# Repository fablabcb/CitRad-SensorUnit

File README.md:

# CitRad - Citizen Science Traffic Radar 

Here you find all the sources about how to build our traffic counter radar system. Find more about the project in general on our [project page](https://community.fablab-cottbus.de/t/ueber-das-cityradar-projekt/453). Discussions about the prototype development you find [here](https://community.fablab-cottbus.de/t/cityradar-teensy-prototyp/492/9). Also we have a separate discussion page about the [development of the casing](https://community.fablab-cottbus.de/t/gehaeusebau-fuer-die-radarsensorelektronik/507).

More details are in the [Software README]() and the [Hardware README](https://github.com/fablabcb/CityRadar/tree/main/Hardware#readme).

## Archive

In the beginning we started to develop a low noise amplifier for the radar module that we didn't need in the end. You find all about this in the [low-noise-amplifier branch](https://github.com/fablabcb/CityRadar/tree/low-noise-amplifier) and on the [discussion page in our forum](https://community.fablab-cottbus.de/t/citrad-elektronik-entwicklung/454)

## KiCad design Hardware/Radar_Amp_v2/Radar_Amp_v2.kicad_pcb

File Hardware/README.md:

# CitRad 3D-Druck und Lasercut Teile

Die detaillierte Bauanleitung findet sich unter [citrad.de/docs/Bauanleitung](https://citrad.de/docs/bauanleitung/). 

Hier finden sich die Lasercut- und 3D-Druck Teile:

- Mit dem Lasercutter die Einlegeplatte 'CasingInlay.svg' aus 3mm Acryl oder ähnlichem schneiden. Bei mehreren `CasingInlay_6x.svg` verwenden.
- Die Mstbefestigung `MastFastening.svg` und die Abstandhalter `MastFasteningWasher.svg` aus 5mm Acryl oder ähnlichem schneiden.
- `SensorRadarMount.scad` in [OpenSCAD](https://openscad.org/) öffnen, als STL exportieren und dann 3D-drucken

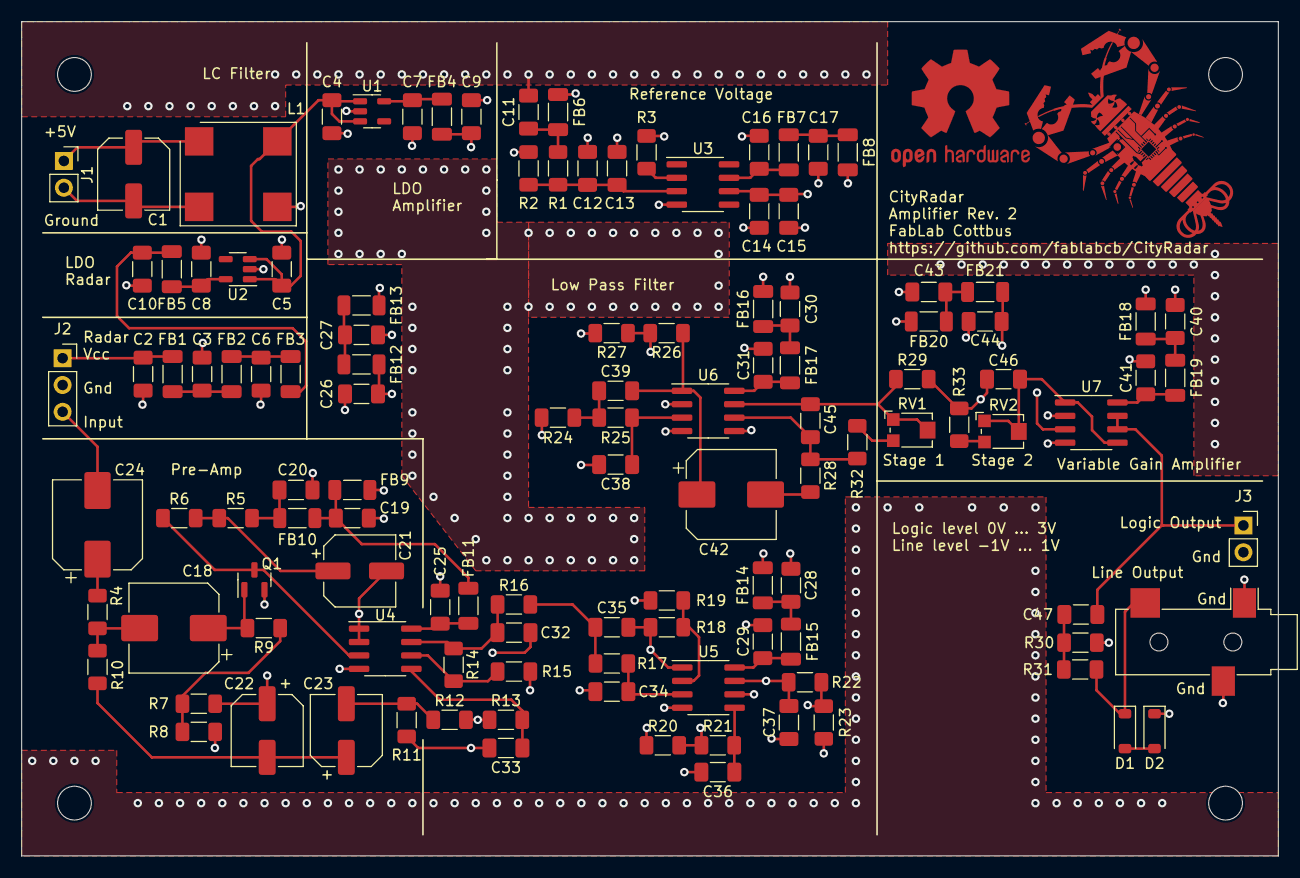
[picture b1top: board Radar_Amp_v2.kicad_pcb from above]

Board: 4 copper layers, 119.0 x 79.0 mm, 123 parts (0 on the bottom side), 67 nets.

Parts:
C1: 100µ; C_Elec_6.3x7.7
C2: 1n; C_1206_3216Metric_Pad1.33x1.80mm_HandSolder
C3, C13, C15, C16, C20, C25, C26, C29, C31, C41, C44: 100n; C_1206_3216Metric_Pad1.33x1.80mm_HandSolder
C4, C5, C6, C7, C8, C12, C14, C19: 10µ; C_1206_3216Metric_Pad1.33x1.80mm_HandSolder
C9, C10, C11, C17: 1µ; C_1206_3216Metric_Pad1.33x1.80mm_HandSolder
C18, C24, C42: 470µ; CP_Elec_8x10
C21, C22, C23: 220µ; C_Elec_6.3x7.7
C27, C28, C30, C40, C43: 1u; C_1206_3216Metric_Pad1.33x1.80mm_HandSolder
C32, C33, C34, C35, C36, C37, C38, C39: 16n; C_1206_3216Metric_Pad1.33x1.80mm_HandSolder
C45, C46: 4p7; C_1206_3216Metric_Pad1.33x1.80mm_HandSolder
C47: 47µ; C_1206_3216Metric_Pad1.33x1.80mm_HandSolder
D1, D2: 1V8; D_SOD-123
FB1, FB2, FB3, FB4, FB5, FB6, FB7, FB8, FB9, FB10, FB11, FB12, FB13, FB14, FB15, FB16, FB17, FB18, FB19, FB20, FB21: 1k@100MHz; L_1206_3216Metric_Pad1.22x1.90mm_HandSolder
H1, H2, H3, H4: MountingHole; MountingHole_3.2mm_M3
J1: Conn_Supply; PinSocket_1x02_P2.54mm_Vertical
J2: Conn_Radar; PinSocket_1x03_P2.54mm_Vertical
J3: Conn_Output_I; PinSocket_1x02_P2.54mm_Vertical
J4: Jack_Output; Jack_3.5mm_CUI_SJ-3523-SMT_Horizontal
L1: Choke_1m; Bourns_SRF1006
Q1: BC847; SOT-23
R1, R2, R9, R10, R11: 1k; R_1206_3216Metric_Pad1.30x1.75mm_HandSolder
R3: 4k99; R_1206_3216Metric_Pad1.30x1.75mm_HandSolder
R4: 10; R_1206_3216Metric_Pad1.30x1.75mm_HandSolder
R5, R6: 2k2; R_1206_3216Metric_Pad1.30x1.75mm_HandSolder
R7: 820; R_1206_3216Metric_Pad1.30x1.75mm_HandSolder
R8: 470; R_1206_3216Metric_Pad1.30x1.75mm_HandSolder
R12, R23: 549; R_1206_3216Metric_Pad1.30x1.75mm_HandSolder
R13: 1k78; R_1206_3216Metric_Pad1.30x1.75mm_HandSolder
R14, R24: 2k15; R_1206_3216Metric_Pad1.30x1.75mm_HandSolder
R15: 976; R_1206_3216Metric_Pad1.30x1.75mm_HandSolder
R16: 365; R_1206_3216Metric_Pad1.30x1.75mm_HandSolder
R17: 2k67; R_1206_3216Metric_Pad1.30x1.75mm_HandSolder
R18: 2k49; R_1206_3216Metric_Pad1.30x1.75mm_HandSolder
R19: 649; R_1206_3216Metric_Pad1.30x1.75mm_HandSolder
R20: 316; R_1206_3216Metric_Pad1.30x1.75mm_HandSolder
R21: 3k09; R_1206_3216Metric_Pad1.30x1.75mm_HandSolder
R22: 2k55; R_1206_3216Metric_Pad1.30x1.75mm_HandSolder
R25: 4k53; R_1206_3216Metric_Pad1.30x1.75mm_HandSolder
R26: 357; R_1206_3216Metric_Pad1.30x1.75mm_HandSolder
R27: 2k74; R_1206_3216Metric_Pad1.30x1.75mm_HandSolder
R28, R29, R32, R33: 100; R_1206_3216Metric_Pad1.30x1.75mm_HandSolder
R30: 10k; R_1206_3216Metric_Pad1.30x1.75mm_HandSolder
R31: 300; R_1206_3216Metric_Pad1.30x1.75mm_HandSolder
RV1, RV2: 10k; Potentiometer_Bourns_TC33X_Vertical
SYM1: Logo_Open_Hardware_Small; OSHW-Logo2_14.6x12mm_Copper
U1, U2: TPS7A2033PDBVR; SOT-23-5
U3: AD8031; SOIC-8_3.9x4.9mm_P1.27mm
U4, U5, U6, U7: AD8656; SOIC-8_3.9x4.9mm_P1.27mm

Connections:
+3.3V: C10.1, FB3.2, FB5.2
+3.3VA: C9.1, FB4.2, FB6.2, FB8.1, FB9.2, FB14.2, FB16.2, FB18.2
/Low-Pass Filter (40dB)/Vref_LPF: C26.1, C33.2, C34.2, C36.2, C38.2, FB12.1, R11.1, R15.2, R19.2, R23.2, R27.2
/Low-Pass Filter (40dB)/input_lpf: C23.2, R11.2, R12.1
/Low-Pass Filter (40dB)/output_lpf: C39.2, C42.1, R26.1, U6.1
/Output Connectors/input_output: C47.1, J3.1, U7.6 (-), U7.7
/Radar_I: C24.2, J2.3
/Vref: C14.1, C15.1, FB13.2, FB20.2, R3.2, U3.6 (Out)
GND: C2.2, C3.2, C4.2, C5.2, C6.2, C7.2, C8.2, C9.2, C10.2, C11.2, C12.2, C13.2, C14.2, C15.2, C16.2, C17.2, C19.2, C20.2, C25.2, C26.2, C27.2, C28.2, C29.2, C30.2, C31.2, C40.2, C41.2, C43.2, C44.2, D2.1 (K), J2.2, J3.2, J4.R, J4.S, L1.3, Q1.2 (E), R2.2, R8.1, R30.1, U1.2 (GND), U2.2 (GND), U3.4 (Vs-), U4.4 (V-), U5.4 (V-), U6.4 (V-), U7.4 (V-)
unnamed: C3.1, FB1.2, FB2.1
unnamed: C6.1, FB2.2, FB3.1
unnamed: C11.1, FB6.1, R1.1
unnamed: C17.1, FB7.2, FB8.2
unnamed: C18.2, R4.2, R10.2
unnamed: C19.1, FB9.1, FB10.2, FB11.2
unnamed: C20.1, FB10.1, R5.2
unnamed: C21.1, R5.1, R6.2
unnamed: C22.2, C23.1, R10.1
unnamed: C24.1, R4.1
unnamed: C27.1, FB12.2, FB13.1
unnamed: C28.1, FB14.1, FB15.2
unnamed: C30.1, FB16.1, FB17.2
unnamed: C32.1, R12.2, R13.1
unnamed: C32.2, R14.1, R16.1, U4.7
unnamed: C35.1, R16.2, R17.1
unnamed: C35.2, R18.1, R20.1, U5.1
unnamed: C37.1, R20.2, R21.1
unnamed: C37.2, R22.1, R24.1, U5.7
unnamed: C39.1, R24.2, R25.1
unnamed: C40.1, FB18.1, FB19.2
unnamed: C42.2, R28.1
unnamed: C43.1, FB20.1, FB21.2
unnamed: C45.2, R29.1, RV1.1, RV1.2, U6.7
unnamed: C47.2, R30.2, R31.1
unnamed: D1.2 (A), D2.2 (A)
unnamed: D1.1 (K), J4.T, R31.2
unnamed: C1.1, J1.1, L1.1
unnamed: C1.2, J1.2, L1.4
unnamed: C2.1, FB1.1, J2.1
unnamed: C18.1, Q1.1 (B), R9.2
unnamed: Q1.3 (C), R6.1, U4.3 (+)
unnamed: R7.1, R8.2, R9.1
unnamed: R32.2, RV1.3
unnamed: R33.2, RV2.3
unnamed: C4.1, C5.1, L1.2, U1.1 (IN), U1.3 (EN), U2.1 (IN), U2.3 (EN)
unnamed: C7.1, FB4.1, U1.5 (OUT)
unnamed: C8.1, FB5.1, U2.5 (OUT)
unnamed: C12.1, C13.1, R1.2, R2.1, U3.3 (IN+)
unnamed: R3.1, U3.2 (IN-)
unnamed: C16.1, FB7.1, U3.7 (Vs+)
unnamed: C21.2, C22.1, R7.2, U4.1, U4.2 (-)
unnamed: C33.1, R13.2, U4.5 (+)
unnamed: R14.2, R15.1, U4.6 (-)
unnamed: C25.1, FB11.1, U4.8 (V+)
unnamed: C34.1, R17.2, U5.3 (+)
unnamed: R18.2, R19.1, U5.2 (-)
unnamed: C36.1, R21.2, U5.5 (+)
unnamed: R22.2, R23.1, U5.6 (-)
unnamed: C29.1, FB15.1, U5.8 (V+)
unnamed: C38.1, R25.2, U6.3 (+)
unnamed: R26.2, R27.1, U6.2 (-)
unnamed: C44.1, FB21.1, U6.5 (+), U7.3 (+)
unnamed: C45.1, R28.2, R32.1, U6.6 (-)
unnamed: C31.1, FB17.1, U6.8 (V+)
unnamed: C46.1, R29.2, R33.1, U7.2 (-)
unnamed: C46.2, RV2.1, RV2.2, U7.1, U7.5 (+)
unnamed: C41.1, FB19.1, U7.8 (V+)

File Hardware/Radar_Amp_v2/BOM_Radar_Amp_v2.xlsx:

Qty | Reference(s) | Value | Footprint | Manufacture #
1 | C1 | 100µ | Capacitor_SMD:C_Elec_6.3x7.7 | 865060343005
1 | C2 | 1n | Capacitor_SMD:C_1206_3216Metric_Pad1.33x1.80mm_HandSolder | C1206C102M5RACTU
11 | C3, C13, C15, C16, C20, C25, C26, C29, C31, C41, C44 | 100n | Capacitor_SMD:C_1206_3216Metric_Pad1.33x1.80mm_HandSolder | C1206C104M5RACTU
8 | C4, C5, C6, C7, C8, C12, C14, C19 | 10µ | Capacitor_SMD:C_1206_3216Metric_Pad1.33x1.80mm_HandSolder | C1206C106K4RACTU
4 | C9, C10, C11, C17 | 1µ | Capacitor_SMD:C_1206_3216Metric_Pad1.33x1.80mm_HandSolder | C1206C105K4RACTU
3 | C18, C24, C42 | 470µ | Capacitor_SMD:CP_Elec_8x10 | 865080353015
3 | C21, C22, C23 | 220µ | Capacitor_SMD:C_Elec_6.3x7.7 | 865060345007
5 | C27, C28, C30, C40, C43 | 1u | Capacitor_SMD:C_1206_3216Metric_Pad1.33x1.80mm_HandSolder | C1206C104M5RACTU
8 | C32, C33, C34, C35, C36, C37, C38, C39 | 16n | Capacitor_SMD:C_1206_3216Metric_Pad1.33x1.80mm_HandSolder | GRM3195C1H163JA01D
2 | C45, C46 | 4p7 | Capacitor_SMD:C_1206_3216Metric_Pad1.33x1.80mm_HandSolder | C1206C479C2GACTU
1 | C47 | 47µ | Capacitor_SMD:C_1206_3216Metric_Pad1.33x1.80mm_HandSolder | C3216X5R1E476M160AC
2 | D1, D2 | 1V8 | Diode_SMD:D_SOD-123 | MMSZ4678-TP
21 | FB1, FB2, FB3, FB4, FB5, FB6, FB7, FB8, FB9, FB10, FB11, FB12, FB13, FB14, FB15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 | 1k@100MHz | Inductor_SMD:L_1206_3216Metric_Pad1.22x1.90mm_HandSolder | BLM31KN102SN1L
1 | J4 | Jack_Output | Connector_Audio:Jack_3.5mm_CUI_SJ-3523-SMT_Horizontal | SJ-3523-SMT-TR
1 | L1 | Choke_1m | radaramp_footprints:Bourns_SRF1006 | SRF1006-102Y
1 | Q1 | BC847 | Package_TO_SOT_SMD:SOT-23 | BC847C,215
5 | R1, R2, R9, R10, R11 | 1k | Resistor_SMD:R_1206_3216Metric_Pad1.30x1.75mm_HandSolder | CR1206-FX-1002ELF
1 | R3 | 4k99 | Resistor_SMD:R_1206_3216Metric_Pad1.30x1.75mm_HandSolder | CR1206-FX-4991ELF
1 | R4 | 10 | Resistor_SMD:R_1206_3216Metric_Pad1.30x1.75mm_HandSolder | CR1206-FX-10R0ELF
2 | R5, R6 | 2k2 | Resistor_SMD:R_1206_3216Metric_Pad1.30x1.75mm_HandSolder | CR1206-FX-2202ELF
1 | R7 | 820 | Resistor_SMD:R_1206_3216Metric_Pad1.30x1.75mm_HandSolder | CR1206-FX-8200ELF
1 | R8 | 470 | Resistor_SMD:R_1206_3216Metric_Pad1.30x1.75mm_HandSolder | CR1206-FX-4700ELF
2 | R12, R23 | 549 | Resistor_SMD:R_1206_3216Metric_Pad1.30x1.75mm_HandSolder | CR1206-FX-5490ELF
1 | R13 | 1k78 | Resistor_SMD:R_1206_3216Metric_Pad1.30x1.75mm_HandSolder | CR1206-FX-1781ELF
2 | R14, R24 | 2k15 | Resistor_SMD:R_1206_3216Metric_Pad1.30x1.75mm_HandSolder | CR1206-FX-2151ELF
1 | R15 | 976 | Resistor_SMD:R_1206_3216Metric_Pad1.30x1.75mm_HandSolder | RC1206FR-07976RL
1 | R16 | 365 | Resistor_SMD:R_1206_3216Metric_Pad1.30x1.75mm_HandSolder | CR1206-FX-3650ELF
1 | R17 | 2k67 | Resistor_SMD:R_1206_3216Metric_Pad1.30x1.75mm_HandSolder | CR1206-FX-2671ELF
1 | R18 | 2k49 | Resistor_SMD:R_1206_3216Metric_Pad1.30x1.75mm_HandSolder | CR1206-FX-2491ELF
1 | R19 | 649 | Resistor_SMD:R_1206_3216Metric_Pad1.30x1.75mm_HandSolder | CR1206-FX-6490ELF
1 | R20 | 316 | Resistor_SMD:R_1206_3216Metric_Pad1.30x1.75mm_HandSolder | CR1206-FX-3160ELF
1 | R21 | 3k09 | Resistor_SMD:R_1206_3216Metric_Pad1.30x1.75mm_HandSolder | CR1206-FX-3091ELF
1 | R22 | 2k55 | Resistor_SMD:R_1206_3216Metric_Pad1.30x1.75mm_HandSolder | CR1206-FX-2551ELF
1 | R25 | 4k53 | Resistor_SMD:R_1206_3216Metric_Pad1.30x1.75mm_HandSolder | CR1206-FX-4531ELF
1 | R26 | 357 | Resistor_SMD:R_1206_3216Metric_Pad1.30x1.75mm_HandSolder | CR1206-FX-3570ELF
1 | R27 | 2k74 | Resistor_SMD:R_1206_3216Metric_Pad1.30x1.75mm_HandSolder | CR1206-FX-2741ELF
4 | R28, R29, R32, R33 | 100 | Resistor_SMD:R_1206_3216Metric_Pad1.30x1.75mm_HandSolder | CR1206-FX-1000ELF
1 | R30 | 10k | Resistor_SMD:R_1206_3216Metric_Pad1.30x1.75mm_HandSolder | CR1206-FX-1002ELF
1 | R31 | 300 | Resistor_SMD:R_1206_3216Metric_Pad1.30x1.75mm_HandSolder | CR1206-FX-3000ELF
2 | RV1, RV2 | 10k | Potentiometer_SMD:Potentiometer_Bourns_TC33X_Vertical | TC33X-2-103E
2 | U1, U2 | TPS7A2033PDBVR | Package_TO_SOT_SMD:SOT-23-5 | TPS7A2033PDBVR
1 | U3 | AD8031 | Package_SO:SOIC-8_3.9x4.9mm_P1.27mm | AD8031ARZ
4 | U4, U5, U6, U7 | AD8656 | Package_SO:SOIC-8_3.9x4.9mm_P1.27mm | AD8656ARZ

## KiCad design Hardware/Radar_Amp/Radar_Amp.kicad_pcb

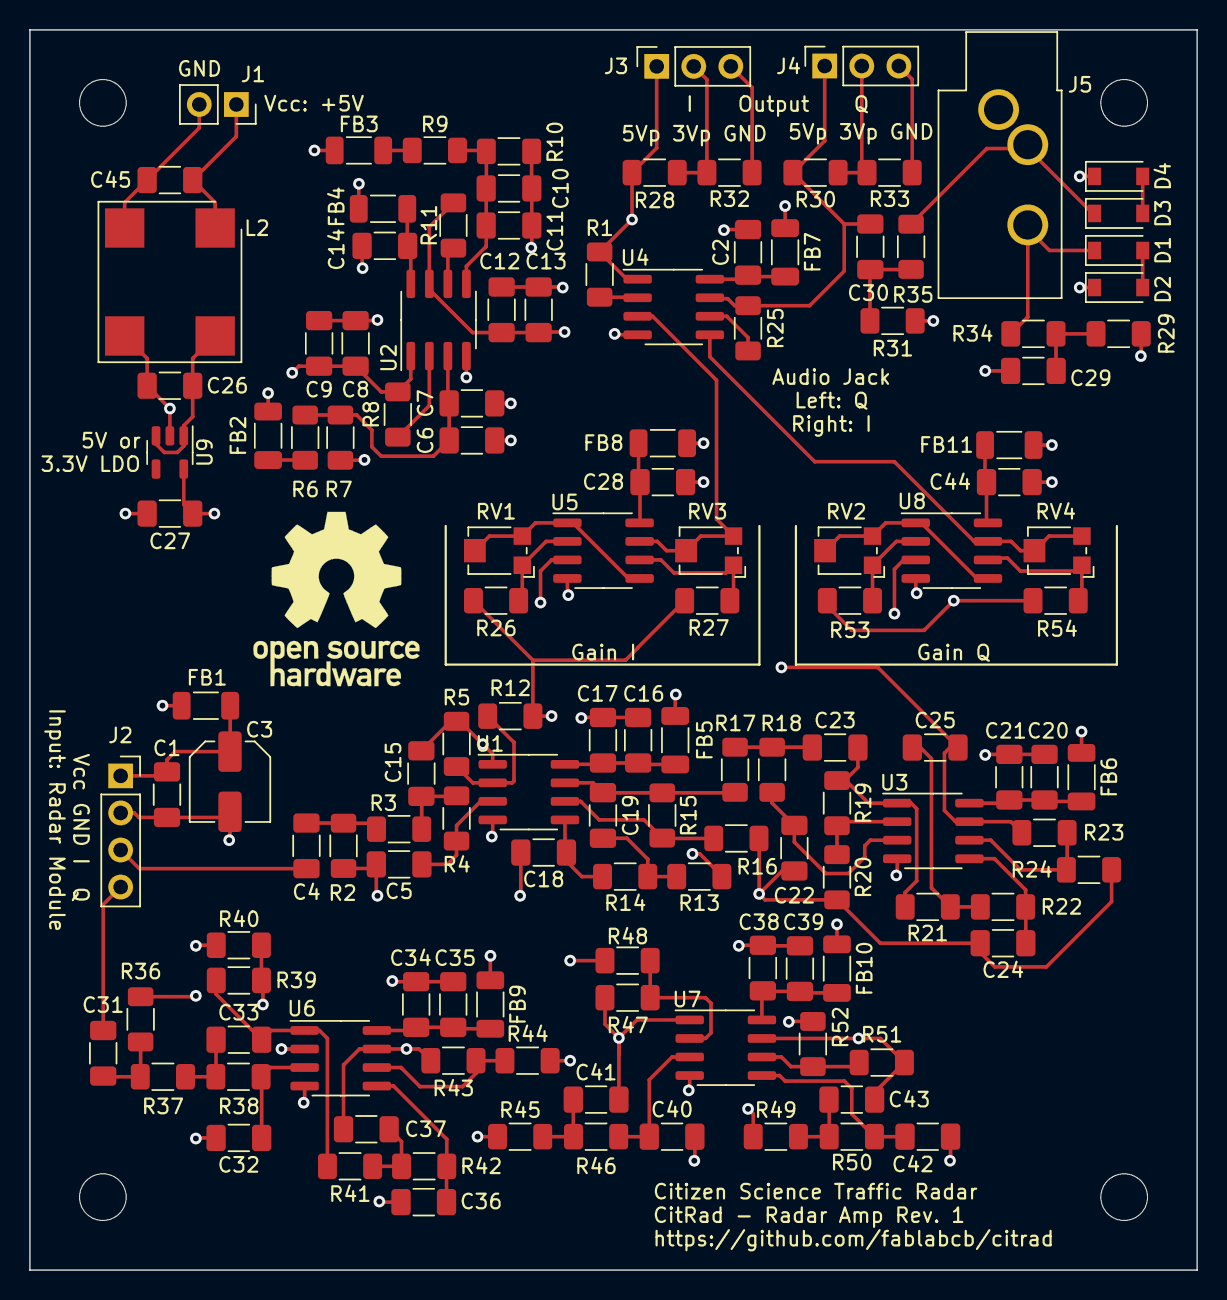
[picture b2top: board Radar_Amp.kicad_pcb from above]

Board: 4 copper layers, 80.0 x 85.0 mm, 137 parts (0 on the bottom side), 78 nets.

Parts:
C1, C7, C9, C11, C13, C17, C21, C35, C39: 100n; C_1206_3216Metric_Pad1.33x1.80mm_HandSolder
C2, C14, C26, C27, C28, C44, C45: 1µ; C_1206_3216Metric_Pad1.33x1.80mm_HandSolder
C3: 10µ; C_Elec_5x5.4
C4, C29, C30, C31: 22µ; C_1206_3216Metric_Pad1.33x1.80mm_HandSolder
C5, C15, C18, C19, C22, C23, C25, C32, C33, C36, C37, C40, C41, C43: 16n; C_1206_3216Metric_Pad1.33x1.80mm_HandSolder
C6, C8, C10, C12, C16, C20, C34, C38: 10µ; C_1206_3216Metric_Pad1.33x1.80mm_HandSolder
C24, C42: 1n6; C_1206_3216Metric_Pad1.33x1.80mm_HandSolder
D1, D2, D3, D4: 1V8; D_SOD-123
FB1, FB2, FB3, FB4, FB5, FB6, FB7, FB8, FB9, FB10, FB11: 1k@100MHz; L_1206_3216Metric_Pad1.22x1.90mm_HandSolder
H1, H2, H3, H4: MountingHole; MountingHole_3.2mm_M3
J1: Conn_Supply; PinSocket_1x02_P2.54mm_Vertical
J2: Conn_Radar; PinSocket_1x04_P2.54mm_Vertical
J3: Conn_Output_I; PinSocket_1x03_P2.54mm_Vertical
J4: Conn_Output_Q; PinSocket_1x03_P2.54mm_Vertical
J5: AudioJack3; Jack_3.5mm_CUI_SJ1-3533NG_Horizontal_CircularHoles
L2: Choke_1m; Bourns_SRF1006
R1, R8, R11, R25: 4k99; R_1206_3216Metric_Pad1.30x1.75mm_HandSolder
R2, R6, R7, R9, R10, R29, R31, R36: 10k; R_1206_3216Metric_Pad1.30x1.75mm_HandSolder
R3, R20, R37, R48: 549; R_1206_3216Metric_Pad1.30x1.75mm_HandSolder
R4, R28, R30, R38: 1k78; R_1206_3216Metric_Pad1.30x1.75mm_HandSolder
R5, R21, R39, R49: 2k15; R_1206_3216Metric_Pad1.30x1.75mm_HandSolder
R12, R40: 976; R_1206_3216Metric_Pad1.30x1.75mm_HandSolder
R13, R41: 365; R_1206_3216Metric_Pad1.30x1.75mm_HandSolder
R14, R32, R33, R42: 2k67; R_1206_3216Metric_Pad1.30x1.75mm_HandSolder
R15, R43: 2k49; R_1206_3216Metric_Pad1.30x1.75mm_HandSolder
R16, R44: 649; R_1206_3216Metric_Pad1.30x1.75mm_HandSolder
R17, R45: 316; R_1206_3216Metric_Pad1.30x1.75mm_HandSolder
R18, R46: 3k09; R_1206_3216Metric_Pad1.30x1.75mm_HandSolder
R19, R47: 2k55; R_1206_3216Metric_Pad1.30x1.75mm_HandSolder
R22, R50: 4k53; R_1206_3216Metric_Pad1.30x1.75mm_HandSolder
R23, R51: 357; R_1206_3216Metric_Pad1.30x1.75mm_HandSolder
R24, R52: 2k74; R_1206_3216Metric_Pad1.30x1.75mm_HandSolder
R26, R27, R34, R35, R53, R54: 300; R_1206_3216Metric_Pad1.30x1.75mm_HandSolder
RV1, RV2, RV3, RV4: R_Potentiometer; Potentiometer_Bourns_TC33X_Vertical
U1, U6: OPA_LNA_1; SOIC-8_3.9x4.9mm_P1.27mm
U2: OPA_REF; SOIC-8_3.9x4.9mm_P1.27mm
U3, U7: OPA_LNA_2; SOIC-8_3.9x4.9mm_P1.27mm
U4: OPA_DRIVER; SOIC-8_3.9x4.9mm_P1.27mm
U5, U8: OPA_VGA; SOIC-8_3.9x4.9mm_P1.27mm
U9: TPS7A20; SOT-23-5

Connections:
+5V: C27.1, FB1.2, FB2.2, FB3.2, FB4.1, FB5.1, FB6.1, FB7.1, FB8.1, FB9.1, FB10.1, FB11.1, U9.5 (OUT)
/LNA+LPF1/Output: C43.2, R51.1, U7.7, U8.3 (+)
/LNA+LPF/Output: C25.2, R23.1, U3.7, U5.3 (+)
/Output/I: C29.1, J3.1, R1.2, R28.1, U4.1
/Output/Q: C30.1, J4.1, R25.2, R30.1, U4.7
/Radar_I: C4.1, J2.3
/Radar_Q: C31.1, J2.4
/VGA1/Output: RV4.2, RV4.3, U4.5 (+), U8.7
/VGA/Output: RV3.2, RV3.3, U4.3 (+), U5.7
/Vref1: C5.2, C8.1, C9.1, C18.2, C22.2, C24.2, R2.2, R8.2, R12.2, R16.2, R20.2, R24.2, R26.1, R27.1, U2.1
/Vref2: C12.1, C13.1, C32.2, C36.2, C40.2, C42.2, R11.2, R36.2, R40.2, R44.2, R48.2, R52.2, R53.1, R54.1, U2.7
GND: C1.2, C2.2, C3.2, C6.2, C7.2, C8.2, C9.2, C10.2, C11.2, C12.2, C13.2, C14.2, C16.2, C17.2, C20.2, C21.2, C26.2, C27.2, C28.2, C34.2, C35.2, C38.2, C39.2, C44.2, D2.1 (K), D4.1 (K), J2.2, J3.3, J4.3, J5.S, L2.3, R7.2, R10.2, R29.1, R31.1, R32.1, R33.1, U1.4 (V-), U2.4 (V-), U3.4 (V-), U4.4 (V-), U5.4 (V-), U6.4 (V-), U7.4 (V-), U8.4 (V-), U9.2 (GND)
unnamed: C1.1, C3.1, FB1.1, J2.1
unnamed: C2.1, FB7.2, U4.8 (V+)
unnamed: C4.2, R2.1, R3.1
unnamed: C5.1, R4.2, U1.3 (+)
unnamed: C6.1, C7.1, R6.2, R7.1, U2.3 (+)
unnamed: C10.1, C11.1, R9.2, R10.1, U2.5 (+)
unnamed: C14.1, FB4.2, U2.8 (V+)
unnamed: C15.1, R3.2, R4.1
unnamed: C15.2, R5.1, R13.1, U1.1
unnamed: C16.1, C17.1, FB5.2, U1.8 (V+)
unnamed: C18.1, R14.2, U1.5 (+)
unnamed: C19.1, R13.2, R14.1
unnamed: C19.2, R15.1, R17.1, U1.7
unnamed: C20.1, C21.1, FB6.2, U3.8 (V+)
unnamed: C22.1, R18.2, U3.3 (+)
unnamed: C23.1, R17.2, R18.1
unnamed: C23.2, R19.1, R21.1, U3.1
unnamed: C24.1, R22.2, U3.5 (+)
unnamed: C25.1, R21.2, R22.1
unnamed: C28.1, FB8.2, U5.8 (V+)
unnamed: C29.2, R29.2, R34.1
unnamed: C30.2, R31.2, R35.1
unnamed: C31.2, R36.1, R37.1
unnamed: C32.1, R38.2, U6.3 (+)
unnamed: C33.1, R37.2, R38.1
unnamed: C33.2, R39.1, R41.1, U6.1
unnamed: C34.1, C35.1, FB9.2, U6.8 (V+)
unnamed: C36.1, R42.2, U6.5 (+)
unnamed: C37.1, R41.2, R42.1
unnamed: C37.2, R43.1, R45.1, U6.7
unnamed: C38.1, C39.1, FB10.2, U7.8 (V+)
unnamed: C40.1, R46.2, U7.3 (+)
unnamed: C41.1, R45.2, R46.1
unnamed: C41.2, R47.1, R49.1, U7.1
unnamed: C42.1, R50.2, U7.5 (+)
unnamed: C43.1, R49.2, R50.1
unnamed: C44.1, FB11.2, U8.8 (V+)
unnamed: C45.1, J1.1, L2.1
unnamed: C45.2, J1.2, L2.4
unnamed: D1.1 (K), J5.R, R34.2
unnamed: D1.2 (A), D2.2 (A)
unnamed: D3.1 (K), J5.T, R35.2
unnamed: D3.2 (A), D4.2 (A)
unnamed: FB2.1, R6.1
unnamed: FB3.1, R9.1
unnamed: J3.2, R28.2, R32.2
unnamed: J4.2, R30.2, R33.2
unnamed: C26.1, L2.2, U9.1 (IN), U9.3 (EN)
unnamed: R1.1, U4.2 (-)
unnamed: R8.1, U2.2 (-)
unnamed: R11.1, U2.6 (-)
unnamed: R5.2, R12.1, U1.2 (-)
unnamed: R15.2, R16.1, U1.6 (-)
unnamed: R19.2, R20.1, U3.2 (-)
unnamed: R23.2, R24.1, U3.6 (-)
unnamed: R25.1, U4.6 (-)
unnamed: R26.2, RV1.1, U5.2 (-)
unnamed: R27.2, RV3.1, U5.6 (-)
unnamed: R39.2, R40.1, U6.2 (-)
unnamed: R43.2, R44.1, U6.6 (-)
unnamed: R47.2, R48.1, U7.2 (-)
unnamed: R51.2, R52.1, U7.6 (-)
unnamed: R53.2, RV2.1, U8.2 (-)
unnamed: R54.2, RV4.1, U8.6 (-)
unnamed: RV1.2, RV1.3, U5.1, U5.5 (+)
unnamed: RV2.2, RV2.3, U8.1, U8.5 (+)

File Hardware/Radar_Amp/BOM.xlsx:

Qty | Reference(s) | Value | LibPart | Footprint | Datasheet | Manufacture #
9 | C1, C7, C9, C11, C13, C17, C21, C35, C39 | 100n | Device:C_Small | Capacitor_SMD:C_1206_3216Metric_Pad1.33x1.80mm_HandSolder | ~ | C1206C104M5RACTU
7 | C2, C14, C26, C27, C28, C44, C45 | 1µ | Device:C_Small | Capacitor_SMD:C_1206_3216Metric_Pad1.33x1.80mm_HandSolder | ~ | C1206C105K4RACTU
1 | C3 | 10µ | Device:C_Small | Capacitor_SMD:C_Elec_5x5.4 | ~ | 865080642006
4 | C4, C29, C30, C31 | 22µ | Device:C_Small | Capacitor_SMD:C_1206_3216Metric_Pad1.33x1.80mm_HandSolder | ~ | GRM31CR71A226KE15L
14 | C5, C15, C18, C19, C22, C23, C25, C32, C33, C36, C37, C40, C41, C43 | 16n | Device:C_Small | Capacitor_SMD:C_1206_3216Metric_Pad1.33x1.80mm_HandSolder | ~ | GRM3195C1H163JA01D
8 | C6, C8, C10, C12, C16, C20, C34, C38 | 10µ | Device:C_Small | Capacitor_SMD:C_1206_3216Metric_Pad1.33x1.80mm_HandSolder | ~ | GRM31CR71E106KA12L
2 | C24, C42 | 1n6 | Device:C_Small | Capacitor_SMD:C_1206_3216Metric_Pad1.33x1.80mm_HandSolder | ~ | GRM3195C2A162JA01D
4 | D1, D2, D3, D4 | 1V8 | Device:D_Zener | Diode_SMD:D_SOD-123 | ~ | MMSZ4678-TP
11 | FB1, FB2, FB3, FB4, FB5, FB6, FB7, FB8, FB9, FB10, FB11 | 1k@100MHz | Device:FerriteBead_Small | Inductor_SMD:L_1206_3216Metric_Pad1.22x1.90mm_HandSolder | ~ | BLM31KN102SN1L
1 | J5 | AudioJack3 | Connector:AudioJack3 | Connector_Audio:Jack_3.5mm_CUI_SJ1-3533NG_Horizontal_CircularHoles | ~ | SJ1-3533NG
1 | L2 | Choke_1m | Device:L_Coupled_1243 | radaramp_footprints:Bourns_SRF1006 | ~ | SRF1006-102Y
4 | R1, R8, R11, R25 | 4k99 | Device:R | Resistor_SMD:R_1206_3216Metric_Pad1.30x1.75mm_HandSolder | ~ | CR1206-FX-4991ELF
8 | R2, R6, R7, R9, R10, R29, R31, R36 | 10k | Device:R | Resistor_SMD:R_1206_3216Metric_Pad1.30x1.75mm_HandSolder | ~ | CR1206-FX-1002ELF
4 | R3, R20, R37, R48 | 549 | Device:R | Resistor_SMD:R_1206_3216Metric_Pad1.30x1.75mm_HandSolder | ~ | CR1206-FX-5490ELF
4 | R4, R28, R30, R38 | 1k78 | Device:R | Resistor_SMD:R_1206_3216Metric_Pad1.30x1.75mm_HandSolder | ~ | CR1206-FX-1781ELF
4 | R5, R21, R39, R49 | 2k15 | Device:R | Resistor_SMD:R_1206_3216Metric_Pad1.30x1.75mm_HandSolder | ~ | CR1206-FX-2151ELF
2 | R12, R40 | 976 | Device:R | Resistor_SMD:R_1206_3216Metric_Pad1.30x1.75mm_HandSolder | ~ | CRCW1206976RFKEA
2 | R13, R41 | 365 | Device:R | Resistor_SMD:R_1206_3216Metric_Pad1.30x1.75mm_HandSolder | ~ | CR1206-FX-3650ELF
4 | R14, R32, R33, R42 | 2k67 | Device:R | Resistor_SMD:R_1206_3216Metric_Pad1.30x1.75mm_HandSolder | ~ | CR1206-FX-2671ELF
2 | R15, R43 | 2k49 | Device:R | Resistor_SMD:R_1206_3216Metric_Pad1.30x1.75mm_HandSolder | ~ | CR1206-FX-2491ELF
2 | R16, R44 | 649 | Device:R | Resistor_SMD:R_1206_3216Metric_Pad1.30x1.75mm_HandSolder | ~ | CR1206-FX-6490ELF
2 | R17, R45 | 316 | Device:R | Resistor_SMD:R_1206_3216Metric_Pad1.30x1.75mm_HandSolder | ~ | CR1206-FX-3160ELF
2 | R18, R46 | 3k09 | Device:R | Resistor_SMD:R_1206_3216Metric_Pad1.30x1.75mm_HandSolder | ~ | RC1206FR-073K09L
2 | R19, R47 | 2k55 | Device:R | Resistor_SMD:R_1206_3216Metric_Pad1.30x1.75mm_HandSolder | ~ | CR1206-FX-2551ELF
2 | R22, R50 | 4k53 | Device:R | Resistor_SMD:R_1206_3216Metric_Pad1.30x1.75mm_HandSolder | ~ | CR1206-FX-4531ELF
2 | R23, R51 | 357 | Device:R | Resistor_SMD:R_1206_3216Metric_Pad1.30x1.75mm_HandSolder | ~ | CR1206-FX-3570ELF
2 | R24, R52 | 2k74 | Device:R | Resistor_SMD:R_1206_3216Metric_Pad1.30x1.75mm_HandSolder | ~ | CR1206-FX-2741ELF
6 | R26, R27, R34, R35, R53, R54 | 300 | Device:R | Resistor_SMD:R_1206_3216Metric_Pad1.30x1.75mm_HandSolder | ~ | CR1206-FX-3000ELF
4 | RV1, RV2, RV3, RV4 | R_Potentiometer | Device:R_Potentiometer | Potentiometer_SMD:Potentiometer_Bourns_TC33X_Vertical | ~ | TC33X-2-103E
2 | U1, U6 | OPA_LNA_1 | Device:Opamp_Dual | Package_SO:SOIC-8_3.9x4.9mm_P1.27mm | ~ | MCP6497T-E/SN
1 | U2 | OPA_REF | Device:Opamp_Dual | Package_SO:SOIC-8_3.9x4.9mm_P1.27mm | ~ | MCP6497T-E/SN
2 | U3, U7 | OPA_LNA_2 | Device:Opamp_Dual | Package_SO:SOIC-8_3.9x4.9mm_P1.27mm | ~ | MCP6497T-E/SN
1 | U4 | OPA_DRIVER | Device:Opamp_Dual | Package_SO:SOIC-8_3.9x4.9mm_P1.27mm | ~ | MCP6497T-E/SN
2 | U5, U8 | OPA_VGA | Device:Opamp_Dual | Package_SO:SOIC-8_3.9x4.9mm_P1.27mm | ~ | MCP6497T-E/SN
1 | U9 | TPS7A20 | Regulator_Linear:TPS7A0508PDBV | Package_TO_SOT_SMD:SOT-23-5 | https://www.ti.com/lit/ds/symlink/tps7a05.pdf | TPS7A2050PDBVR
 | C1206C104M5RACTU | 32 |  |  | 9
 | C1206C105K4RACTU | 25 |  |  | 7
 | 865080642006 | 4 |  |  | 1
 | GRM31CR71A226KE15L | 14 |  |  | 4
 | GRM3195C1H163JA01D | 49 |  |  | 14
 | GRM31CR71E106KA12L | 28 |  |  | 8
 | GRM3195C2A162JA01D | 7 |  |  | 2
 | MMSZ4678-TP | 14 |  |  | 4
 | BLM31KN102SN1L | 39 |  |  | 11
 | SJ1-3533NG | 4 |  |  | 1
 | SRF1006-102Y | 4 |  |  | 1
 | CR1206-FX-4991ELF | 14 |  |  | 4
 | CR1206-FX-1002ELF | 28 |  |  | 8
 | CR1206-FX-5490ELF | 14 |  |  | 4
 | CR1206-FX-1781ELF | 14 |  |  | 4
 | CR1206-FX-2151ELF | 14 |  |  | 4
 | CRCW1206976RFKEA | 7 |  |  | 2
 | CR1206-FX-3650ELF | 7 |  |  | 2
 | CR1206-FX-2671ELF | 14 |  |  | 4
 | CR1206-FX-2491ELF | 7 |  |  | 2
 | CR1206-FX-6490ELF | 7 |  |  | 2
 | CR1206-FX-3160ELF | 7 |  |  | 2
 | RC1206FR-073K09L | 7 |  |  | 2
 | CR1206-FX-2551ELF | 7 |  |  | 2
 | CR1206-FX-4531ELF | 7 |  |  | 2
 | CR1206-FX-3570ELF | 7 |  |  | 2
 | CR1206-FX-2741ELF | 7 |  |  | 2
 | CR1206-FX-3000ELF | 21 |  |  | 6
 | TC33X-2-103E | 14 |  |  | 4
 | MCP6497T-E/SN | 7 |  |  | 2
 | MCP6497T-E/SN | 4 |  |  | 1
 | MCP6497T-E/SN | 7 |  |  | 2
 | MCP6497T-E/SN | 4 |  |  | 1
 | MCP6497T-E/SN | 7 |  |  | 2
 | TPS7A2050PDBVR | 4 |  |  | 1

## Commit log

2023-06-27 Hardware Rev. 1
2023-06-27 Backup entfernt
2023-08-12 PCB v2
2023-09-14 fixes
2023-10-07 Radar FFT analysis with serial transmit and visualisation in Processing
2023-10-08 variable sample rate; transmit full FFT spectrum
2023-10-08 detect speed from fft spectrum, draw in graph
2023-10-09 variable gain controlled from processing; faster display with PImage instead of rect(); zoom
2023-10-10 README for teensy prototype
2023-10-11 tidying
2023-10-11 transmit raw fft data instead of scaled ones
2023-10-11 switch to 32bit Audio library
2023-10-12 dbfs output from fft; transmit more decimal places but transmit only limited number of fft bins to speed up the transmition
2023-10-12 first test of IQ-fft; reduced transmit decimals to speed up transmission; axis not adapted yet
2023-10-13 transmit data in binary (makes it much faster)
2023-10-16 second Serial for debug messages; IQ-fft documentation in README
2023-10-17 correction for I-Q imbalance
2023-10-18 I and Q channel on left and right headphone
2023-10-21 correct IQ axis; new zoom behavior
2023-10-21 corrected zoom behaviour in IQ graph
2023-10-22 save FFT data to SD card
2023-10-26 write to SD with better format; noise while writing to SD; set time from RTC or computer
2023-10-26 webApp with openstreetmap data; place sensors on street
2023-10-28 write detection data into csv file; write only every x cycles
2023-10-28 commit where I tried to buffer outputs to get around SD card noise
2023-10-29 store 8bit raw data
2023-12-02 detect direction, calculate mean reverse amplitude, fixed IQ tuning not initialize
2024-01-12 realtime clock sync; filename with timestamp (no overwrite of files); distance from noise floor as amplitude threshold; bins_with_signal as trigger for cars passing by
2024-01-12 moved Hardware folder to different branch
2024-01-12 moved Teensy prototype development into Software folder
2024-01-12 Update README.md
    Links to Software and Hardware README
2024-01-12 Readme for the Hardware
2024-01-20 added lots of comments; dominant frequency calculated for both directions
2024-01-20 updated gitignore
2024-01-20 renamed ino file (must have the same name as parent folder)
2024-01-24 fixed compiling errors
2024-02-14 smooth spectrum
2024-09-04 Changed name in README.md
2024-09-12 example rawdata (spectrum) file read and plotting in R
2024-09-13 tests: subtract mirrored spectrum to get rid of ghost signals
2024-09-13 test large file storage (git-lfs)
2024-09-13 Nordring data
2024-09-17 major code refactoring
2024-09-18 feature(SD Card): files can now be split and chip will idle until SD card is inserted
2024-09-22 feature(Config): if SD-Card contains file 'config.txt' then this will overwrite default config values; not all values are supported yet
2024-09-22 added missing file
2024-09-22 feature(File): existing files will not be overwritten; closes #9
2024-09-27 data processing method in R
2024-09-27 feature(File): added write-error detection and file markers; changed file format and incremented file version!
2024-09-27 removed noise floor todo
2024-09-27 feature(File) fixed missing returns
2024-09-27 refactoring(Names): moved more variables to camelCase and restructured result/setup data; refactored audo processing function
2024-10-01 feature(Smoothing): added configurable dynamic_noise_level using running mean; fixed file format issue; closes #12
2024-10-01 feature(Smoothing): added carTriggerSignal output; configurable fields in csv contain parameter in header
2024-10-08 car trigger finetuning in R script
2024-10-16 feature(signalProcessingFromR): restructured processing and finished basic detection
2024-10-30 feature(signalProcessingFromR): implemented basic processing; untested but mostly complete
2024-10-30 updated noise floor (subtracted median)
2024-10-30 feature(signalProcessingFromR): added companion app and finalized migration from R
2024-10-30 removed companion data
2024-11-03 feature(Config): config parsing trims leading and trailing spaces
2024-11-18 cleanup(CSV): removed unused fields; closes #16
2025-01-03 added mobile companion application
2025-01-07 added teensy serial id to files and serial output; closes #15
2025-01-07 simplified timestamp handling in detection data; closes #18
2025-01-07 updated file format documentation; new format is v3
2025-01-08 file cleanup; removed cairoCompanion
2025-01-14 hardware: added sensor mount scad file
2025-01-19 3D-Druck und Lasercut Teile
2025-03-16 FreeCAD Projekt Datei und stls für Magnetschalter bereitgestellt
